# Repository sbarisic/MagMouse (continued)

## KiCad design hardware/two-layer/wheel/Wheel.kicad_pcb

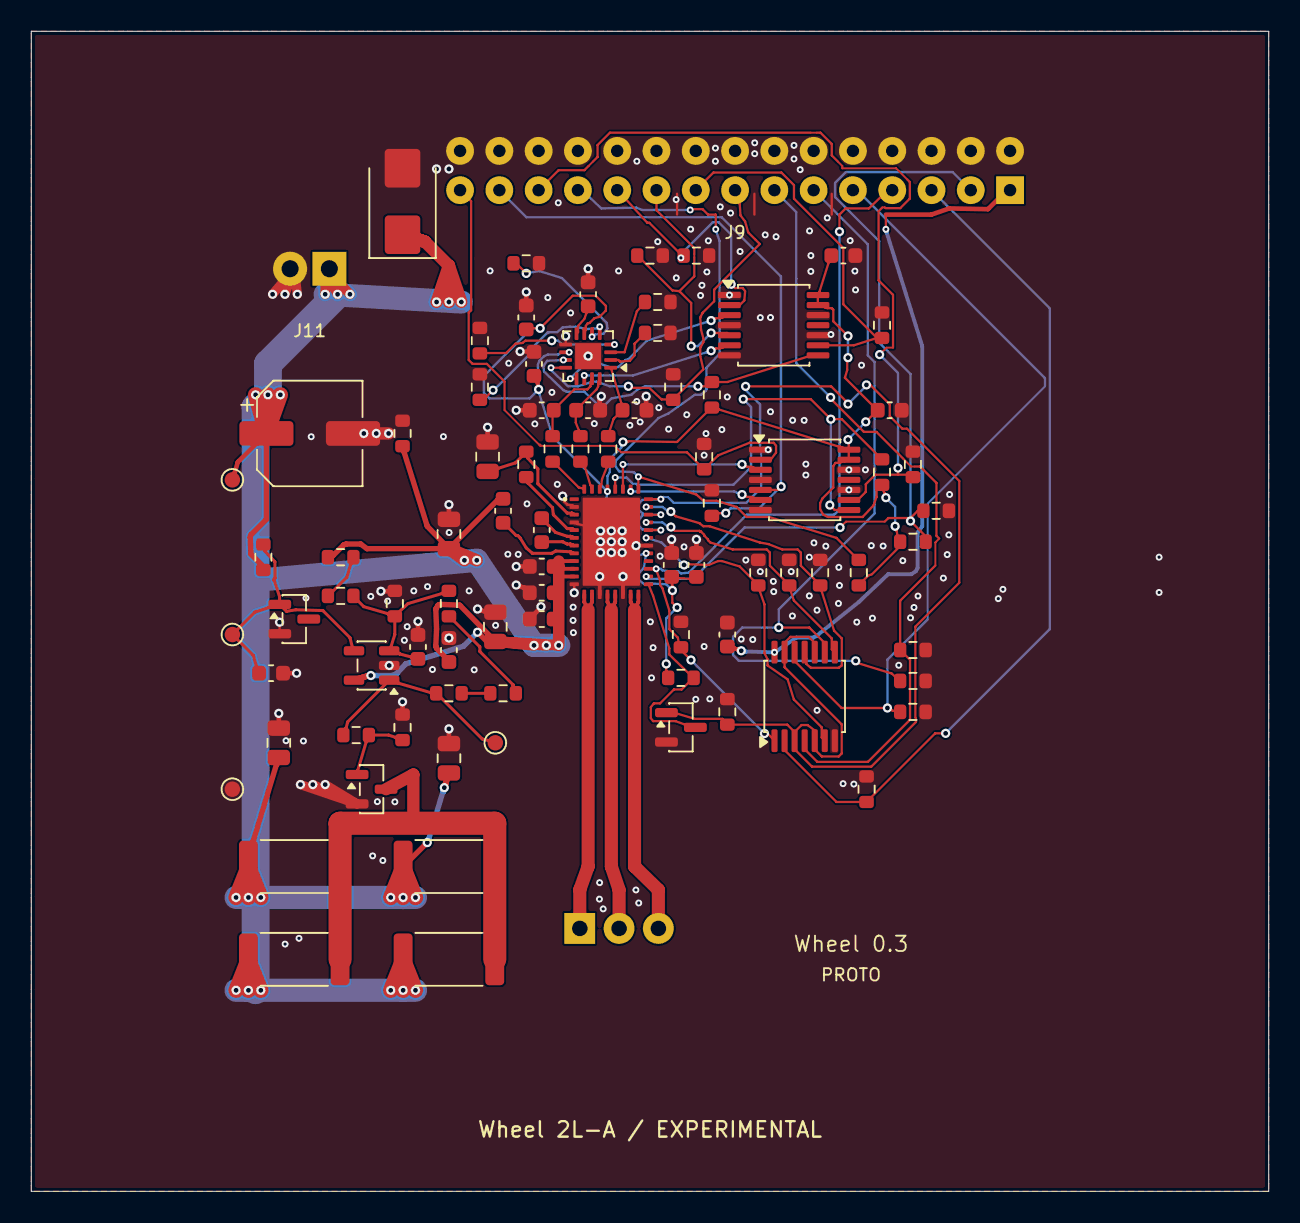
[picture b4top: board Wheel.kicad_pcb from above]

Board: 2 copper layers, 80.0 x 75.0 mm, 87 parts (0 on the bottom side), 57 nets.

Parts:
C41, C42, C43, C49, C51, C52, C54, C65, C66: 100nF; C_0603_1608Metric
C44, C45, C68, C69: 10uF/25V; C_0805_2012Metric
C46, C48, C56, C57, C58: 1uF/50V; C_0603_1608Metric
C47: 47nF/50V; C_0603_1608Metric
C50: 22uF/25V; C_0805_2012Metric
C59, C60, C61, C67: 22pF/50V; C_0603_1608Metric
C90: 100uF/16V; CP_Elec_6.3x5.9
D6: SMBJ6.0A; D_SMB
J5: GB1806 phase wires; MotorWire_3x1mm_P2.54mm
J9: Soldered wires Signal_2x15; Wire_Signal_2x15_P2.54mm
J11: Soldered wires Power_1x02; Wire_Power_1x02_P2.54mm
Q4: 2N7002; SOT-23
Q5: AO3400A; SOT-23
R81: 22R; R_0603_1608Metric
R82, R84, R86, R98, R111, R137, R138, R139, R140: 10k; R_0603_1608Metric
R83, R89, R90, R91, R92, R94, R95, R96, R97, R100, R112, R114, R120: 100k; R_0603_1608Metric
R87, R88, R146: 4.7k; R_0603_1608Metric
R102, R103, R104: 330R; R_0603_1608Metric
R105, R106, R107, R108, R109: 0R; R_0603_1608Metric
R113: 34.8k; R_0603_1608Metric
R115, R116, R117: 1M; R_0603_1608Metric
R119: 100R; R_0603_1608Metric
R121, R122, R123, R124: 47R/2W; R_2512_6332Metric
R144, R145: 33k; R_0603_1608Metric
TP34: ACT_5V; TestPoint_Pad_D1.0mm
TP35: BRAKE_REF; TestPoint_Pad_D1.0mm
TP36: BRAKE_OUT; TestPoint_Pad_D1.0mm
TP37: GND; TestPoint_Pad_D1.0mm
U21: DRV8316RRGFR; Texas_RGF0040E
U22: SN74LVC08APWR; TSSOP-14_4.4x5mm_P0.65mm
U23: ADS7038IRTER; WQFN-16-1EP_3x3mm_P0.5mm_EP1.68x1.68mm
U24, U26: SN74LVC125APWR; TSSOP-14_4.4x5mm_P0.65mm
U30: TLV1811DBVR; SOT-23-5
U31: LM4040AIM3-2.5/NOPB; SOT-23

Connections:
+3V3: C51.1, J9.1, U22.14
ACT_5V: C41.1, C42.1, C43.1, C44.1, C45.1, C46.2, C65.1, C68.1, C69.1, C90.1, D6.1, J11.1, R111.1, R112.1, R121.1, R122.1, R123.1, R124.1, R146.1, TP34.1, U21.9, U21.10, U21.11, U30.5
ACT_DRIVE_EN: J9.7, R84.1, U21.23, U22.1
ADC2_CS_LOCAL: R98.2, U23.11, U26.8
ADC2_DECAP: C58.1, U23.8
ADC2_MISO_LOCAL: J9.15, R100.1, U23.12
ADC2_MOSI_LOCAL: U23.14, U26.6
ADC2_SCLK_LOCAL: U23.13, U26.3
ADC2_SPARE3: R105.1, U23.2
ADC2_SPARE4: R106.1, U23.3
ADC2_SPARE5: R107.1, U23.4
ADC2_SPARE6: R108.1, U23.5
ADC2_SPARE7: R109.1, U23.6
BRAKE_DIV_TOP: R112.2, R113.1
BRAKE_DRAIN: Q5.3, R121.2, R122.2, R123.2, R124.2
BRAKE_FB_1: R115.2, R116.1
BRAKE_FB_2: R116.2, R117.1
BRAKE_GATE: Q5.1, R119.2, R120.1
BRAKE_OUT: R115.1, R119.1, TP36.1, U30.1
BRAKE_REF: C66.1, R111.2, TP35.1, U30.4, U31.1
BRAKE_SENSE: C67.1, R113.2, R114.1, R117.2, U30.3
CS_ADC2: J9.17, R145.1, U26.9
CS_DRV8316: J9.25, R144.1, U24.9
DRV_AVDD: C48.1, C49.1, C52.1, C54.1, C56.1, C57.1, R82.1, R86.1, R87.1, R88.1, R98.1, U21.25, U21.37, U23.7, U23.10, U24.13, U24.14, U26.13, U26.14
DRV_CS_LOCAL: R86.2, U21.36, U24.8
DRV_FAULT_LOCAL_N: J9.3, R88.2, R89.1, U21.22
DRV_INHA: R90.1, U21.27, U22.6
DRV_INHB: R91.1, U21.29, U22.8
DRV_INHC: R92.1, U21.31, U22.11
DRV_MISO_LOCAL: J9.23, R87.2, U21.33
DRV_MOSI_LOCAL: U21.34, U24.6
DRV_SCLK_LOCAL: U21.35, U24.3
GND: C41.2, C42.2, C43.2, C44.2, C45.2, C48.2, C49.2, C50.2, C51.2, C52.2, C54.2, C56.2, C57.2, C58.2, C59.2, C60.2, C61.2, C65.2, C66.2, C67.2, C68.2, C69.2, C90.2, D6.2, J9.2, J9.4, J9.6, J9.8, J9.10, J9.12, J9.14, J9.16, J9.18, J9.20, J9.22, J9.24, J9.26, J9.28, J9.30, J11.2, Q4.2, Q5.2, R83.2, R84.2, R89.2, R90.2, R91.2, R92.2, R94.2, R95.2, R96.2, R97.2, R100.2, R105.2, R106.2, R107.2, R108.2, R109.2, R114.2, R120.2, R137.2, R138.2, R139.2, R140.2, R144.2, R145.2, R146.2, TP37.1, U21.2, U21.4, U21.12, U21.15, U21.18, U21.26, U21.41, U22.7, U23.9, U23.17, U24.1, U24.4, U24.7, U24.10, U24.12, U26.1, U26.4, U26.7, U26.10, U26.12, U30.2, U31.2
MOTOR_SPI_MOSI: J9.19, R97.1, U26.5
MOTOR_SPI_SCLK: J9.21, R96.1, U26.2
SPI_MOSI: J9.27, R95.1, U24.5
SPI_SCLK: J9.29, R94.1, U24.2
WHEEL_BUCK_OUT: C50.1, R81.2, U21.3
WHEEL_BUCK_SW: R81.1, U21.5
WHEEL_CP: C46.1, U21.8
WHEEL_CPH: C47.1, U21.7
WHEEL_CPL: C47.2, U21.6
WHEEL_DRVOFF: Q4.3, R82.2, U21.21
WHEEL_I_A: C59.1, R102.2, U23.15
WHEEL_I_B: C60.1, R103.2, U23.16
WHEEL_I_C: C61.1, R104.2, U23.1
WHEEL_PHASE_A: J5.1, U21.13, U21.14
WHEEL_PHASE_B: J5.2, U21.16, U21.17
WHEEL_PHASE_C: J5.3, U21.19, U21.20
WHEEL_PWM_A: J9.13, R138.1, U22.4
WHEEL_PWM_B: J9.11, R139.1, U22.9
WHEEL_PWM_C: J9.9, R140.1, U22.12
WHEEL_RUN_EN: Q4.1, R83.1, U21.28, U21.30, U21.32, U22.3, U22.5, U22.10, U22.13
WHEEL_RUN_REQ: J9.5, R137.1, U22.2
WHEEL_SOA: R102.1, U21.40
WHEEL_SOB: R103.1, U21.39
WHEEL_SOC: R104.1, U21.38

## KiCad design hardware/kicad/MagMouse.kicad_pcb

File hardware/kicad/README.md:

# KiCad electronics

This directory is the **retained monolithic reference**. Current work uses the
independent [Main project](../modular/main/Main.kicad_pro) and
[Wheel project](../modular/wheel/Wheel.kicad_pro), both now routed with zero
unrouted/DRC/parity issues. See the [modular package](../modular/README.md).
The revision and instructions below describe the older reference project.

Revision 0.8, 2026-09-09, KiCad 10.0.6. USB-C power, MCU allocation and wheel/brake, IMU, RGB and PMW3360 circuits are connected.
A [60 x 95 mm motherboard placement](../pcb/README.md) is available as of
2026-09-09, with all 317 footprints on-board. U27/C62 and J7 are in a separate,
fully routed [14 x 18 mm encoder project](../encoder/README.md). Both are editable
development drafts; **the motherboard is partially routed and neither board is
order-ready**. Firmware, measurements and mechanical fit remain open.

## Open the retained reference

1. Open [MagMouse.kicad_pro](MagMouse.kicad_pro) in KiCad Manager.
2. Open [MagMouse.kicad_sch](MagMouse.kicad_sch).
3. Enter a sheet and press **E** on a component to inspect its MPN, footprint,
   LCSC number and sourcing status.
4. Open [MagMouse.kicad_pcb](MagMouse.kicad_pcb) in PCB Editor for the initial
   layout. Enable Dwgs.User for reservations and F.Fab/B.Fab for references.

Use the standard KiCad 10 libraries. The local symbol and footprint libraries
are registered by [sym-lib-table](sym-lib-table) and [fp-lib-table](fp-lib-table).
No JLCPCB plugin is needed. Edit the schematic files directly.

| Sheet | Implemented content |
| --- | --- |
| Overview | Eighteen-page hierarchy and remaining work |
| 01 Power / USB | USB-C data/CC protection, TUSB320 sink detection, TPS62162 fixed 3.3 V regulator |
| 02 MCU | ESP32-S3 module, USB, reset/boot, recovery pads and power-control GPIOs |
| 03 Buttons | Three DRV8231A bridges, VREF/current feedback, input pulldowns and coil connectors |
| 04 Sensing | Three switchable Hall sensors, ADS7038; all eight ADC channels assigned |
| 05 Protected power | Separate input/actuator eFuses, UVLO/OVLO, ramps, fault/reset and enable clamp |
| 06 Actuator interlock | Hardware heartbeat timeout, source/reset/sensor-qualified arm and six input gates |
| 07 Power monitor | CC-selected current-limit resistors, buffered input-current sensing, VBUS presence and ACT voltage |
| 08 Actuator rail | Input/actuator transient clamps, ACT storage/discharge and test pads |
| 09 Interface reservations | MCU interfaces, test pads and boot/control bias |
| 10 Wheel driver | DRV8316R, 3-PWM hardware shutdown, charge pump, unused-buck termination and motor wire pads |
| 11 Wheel SPI | Driver/ADC2/encoder power-domain buffers and fault return |
| 12 Wheel feedback | Second ADS7038, phase-current filters, switched encoder supply and J6 cable header |
| 13 Regeneration brake | ACT-powered comparator/reference, MOSFET and four power resistors |
| 14 IMU | ICM-42688-P, shared SPI2, INT1 and supply bypass |
| 15 RGB status | Single-data-pin LED, enabled regulator and logic buffer |
| 16 Optical power | Sensor-enabled ramp switch, 1.9V LDO, illumination feed and bypass |
| 17 Optical sensor | PMW3360, isolated SPI/CS and strong reset buffer |

VBUS_USB feeds PWR_5V through U12; U13 supplies ACT_5V. These rails replace the
disconnected pending nets. The TPS62162 and 3.3 uH inductor replace the original
TLV62569/divider circuit. See [power behavior and firmware requirements](../../docs/power.md)
and [power sourcing/package review](POWER_REVIEW.md).

Each button bridge retains the provisional 0.333 A trip setting:
1.65 V / (0.0015 × 3300 ohms). Actual force, current accuracy, winding heating
and pulse duration require the mechanical experiment. Coils, magnets, paddles
and wiring are external assemblies, not SMT parts.

## Review exports

From the repository root, run these commands with Python 3 and KiCad 10:

    python hardware/kicad/export_review.py
    python hardware/kicad/export_review.py --schematic hardware/encoder/Encoder.kicad_sch
    python hardware/kicad/verify_encoder.py
    python hardware/kicad/test_encoder_checks.py
    python hardware/kicad/verify_power.py
    python hardware/kicad/verify_resources.py
    python hardware/kicad/verify_wheel.py
    python hardware/kicad/test_wheel_checks.py
    python hardware/kicad/verify_peripherals.py
    python hardware/kicad/test_peripheral_checks.py
    python hardware/kicad/verify_optical.py
    python hardware/kicad/test_optical_checks.py

The exporter accepts --kicad-cli PATH. The checker accepts --footprints PATH
for a nonstandard KiCad footprint installation. Generated files go to
build/kicad-review: eighteen SVG sheets, XML netlist, ERC JSON, DRAFT-bom.csv,
review-status.json, power-checks.json, resource-checks.json, wheel-checks.json, peripheral-checks.json and optical-checks.json. Sources are not overwritten.

The motherboard has **273 BOM components**, all with catalog IDs, MPNs and
footprints; 43 copper test pads, J5 motor wire pads and four power flags are
excluded from its BOM. The separate encoder has one schematic sheet and three
BOM components/footprints: U27, C62 and J7. Across both projects there are 19
schematic pages, 276 BOM components and 320 footprints. Encoder review outputs
and its separate draft BOM go to `build/encoder-review`; its two incoming power
flags are excluded from assembly. Export both netlists before running the wheel
checker. The encoder checker also verifies the actual harness contract.
**Both projects: ERC zero errors and zero warnings, without new waivers.**
The additional checker verifies 195 critical power pin connections, 317 motherboard footprint
assignments, complete source-to-export coverage and 4,096 Boolean interlock
cases. The resource checker verifies all 39 module GPIOs: 38 assigned and GPIO46
reserved low for boot-safe expansion. See [the full allocation](../../docs/interfaces.md).
The wheel checker adds 266 pin checks, 32 shutdown cases, 58 custom land checks
and 128 brake corners; five wheel tests include four fault injections.
Optical adds 81 pin checks, ten identities, 16 land coordinates and eight fault injections.
See [optical implementation](OPTICAL_DESIGN.md) for pending sample and firmware evidence.
See [wheel design and evidence](WHEEL_REVIEW.md) and [IMU/RGB review](PERIPHERAL_REVIEW.md). Analog timing, firmware
deadlines, thermal behavior and USB compliance are not simulated.

Catalog identity does not reserve stock. U11's current JLCPCB listing requires
Standard PCBA; refresh service eligibility and pricing before placing an order.
These schematic tools do not produce manufacturing files. Use
`python hardware/kicad/export_pcb_review.py` for the separate PCB placement/DRC
review; see [board setup and remaining layout work](../pcb/README.md).
The first [buck routing pass](../pcb/BUCK_LAYOUT.md) also provides native copper
connectivity checks and fault-injection tests, run with KiCad's bundled Python.

## Work before full-board freeze

A bench prototype and preliminary placement can proceed before all measurements
are complete. Full-mouse routing needs settled circuitry, pin allocation and
mechanical dimensions. The following tests are acceptance gates, including tests
that require a prototype PCB; finished firmware is not required to start layout.

- Implement and measure USB startup, configuration, suspend/resume and source
  changes. Verify the 100 mA startup and 2.5 mA suspend requirements.
- Prototype one button; measure force/current, winding properties, current-sense
  accuracy, heating, passive return and magnetic interference.
- Test timeout/reset/short-circuit behavior, cable drop, inrush, reverse current,
  regenerative clamp behavior and component temperatures.
- Qualify the [PMW3360 circuit](OPTICAL_DESIGN.md), samples, SROM and optical stack.
  Review and measure the [IMU/RGB circuits](PERIPHERAL_REVIEW.md). Validate wheel current/angle
  acquisition and the provisional autonomous regeneration brake on hardware.
- Validate the [allocated SPI/PWM timing budgets](../../docs/interfaces.md), review symbols,
  land patterns and stencil requirements, then perform board layout and DRC.

See [SOURCING.md](SOURCING.md) for retained component evidence and
[the roadmap](../../docs/roadmap.md) for the broader project.

The [input-power routing pass](../pcb/INPUT_POWER_LAYOUT.md) adds C88,
USB-to-eFuse-to-buck copper, protection and source-selection routes, and
a board-wide In1 ground reference. USB geometry is recorded in the
[selected stackup](../pcb/STACKUP.md); the [USB/ILM pass](../pcb/USB_LAYOUT.md)
now routes the pair over continuously checked In1 ground. Full-board routing remains open.

The [Type-C routing pass](../pcb/TYPEC_LAYOUT.md) completes the detector inputs,
returns and source-selection supplies. The [U13 local routing pass](../pcb/ACTUATOR_POWER_LAYOUT.md)
adds C89 and connects its feed, bypass and protection network. Native connectivity
has 204 unrouted connections after the [USB/ILM pass](../pcb/USB_LAYOUT.md).
Actuator feeds, driver/brake outputs, current sensing, interlocks and gate supplies
are connected and checked, as are USB data and buffered input-current telemetry.
SPI, optical and remaining board routing are open.
Six component-land vias at U1/C32/U21 require filled/capped fabrication and stencil review.

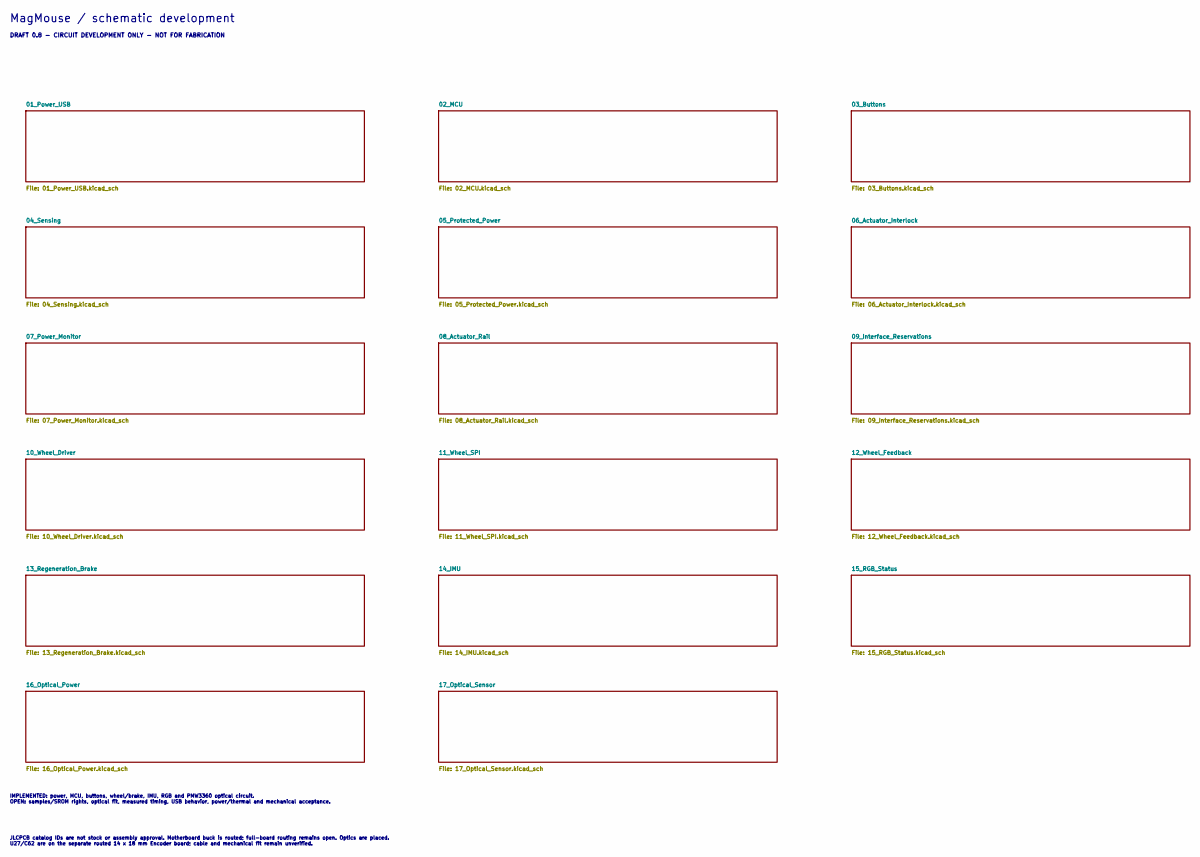
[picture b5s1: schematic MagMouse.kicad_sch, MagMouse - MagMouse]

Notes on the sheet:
MagMouse / schematic development
DRAFT 0.8 - CIRCUIT DEVELOPMENT ONLY - NOT FOR FABRICATION
IMPLEMENTED: power, MCU, buttons, wheel/brake, IMU, RGB and PMW3360 optical circuit. OPEN: samples/SROM rights, optical fit, measured timing, USB behavior, power/thermal and mechanical acceptance.
JLCPCB catalog IDs are not stock or assembly approval. Motherboard buck is routed; full-board routing remains open. Optics are placed. U27/C62 are on the separate routed 14 x 18 mm Encoder board; cable and mechanical fit remain unverified.

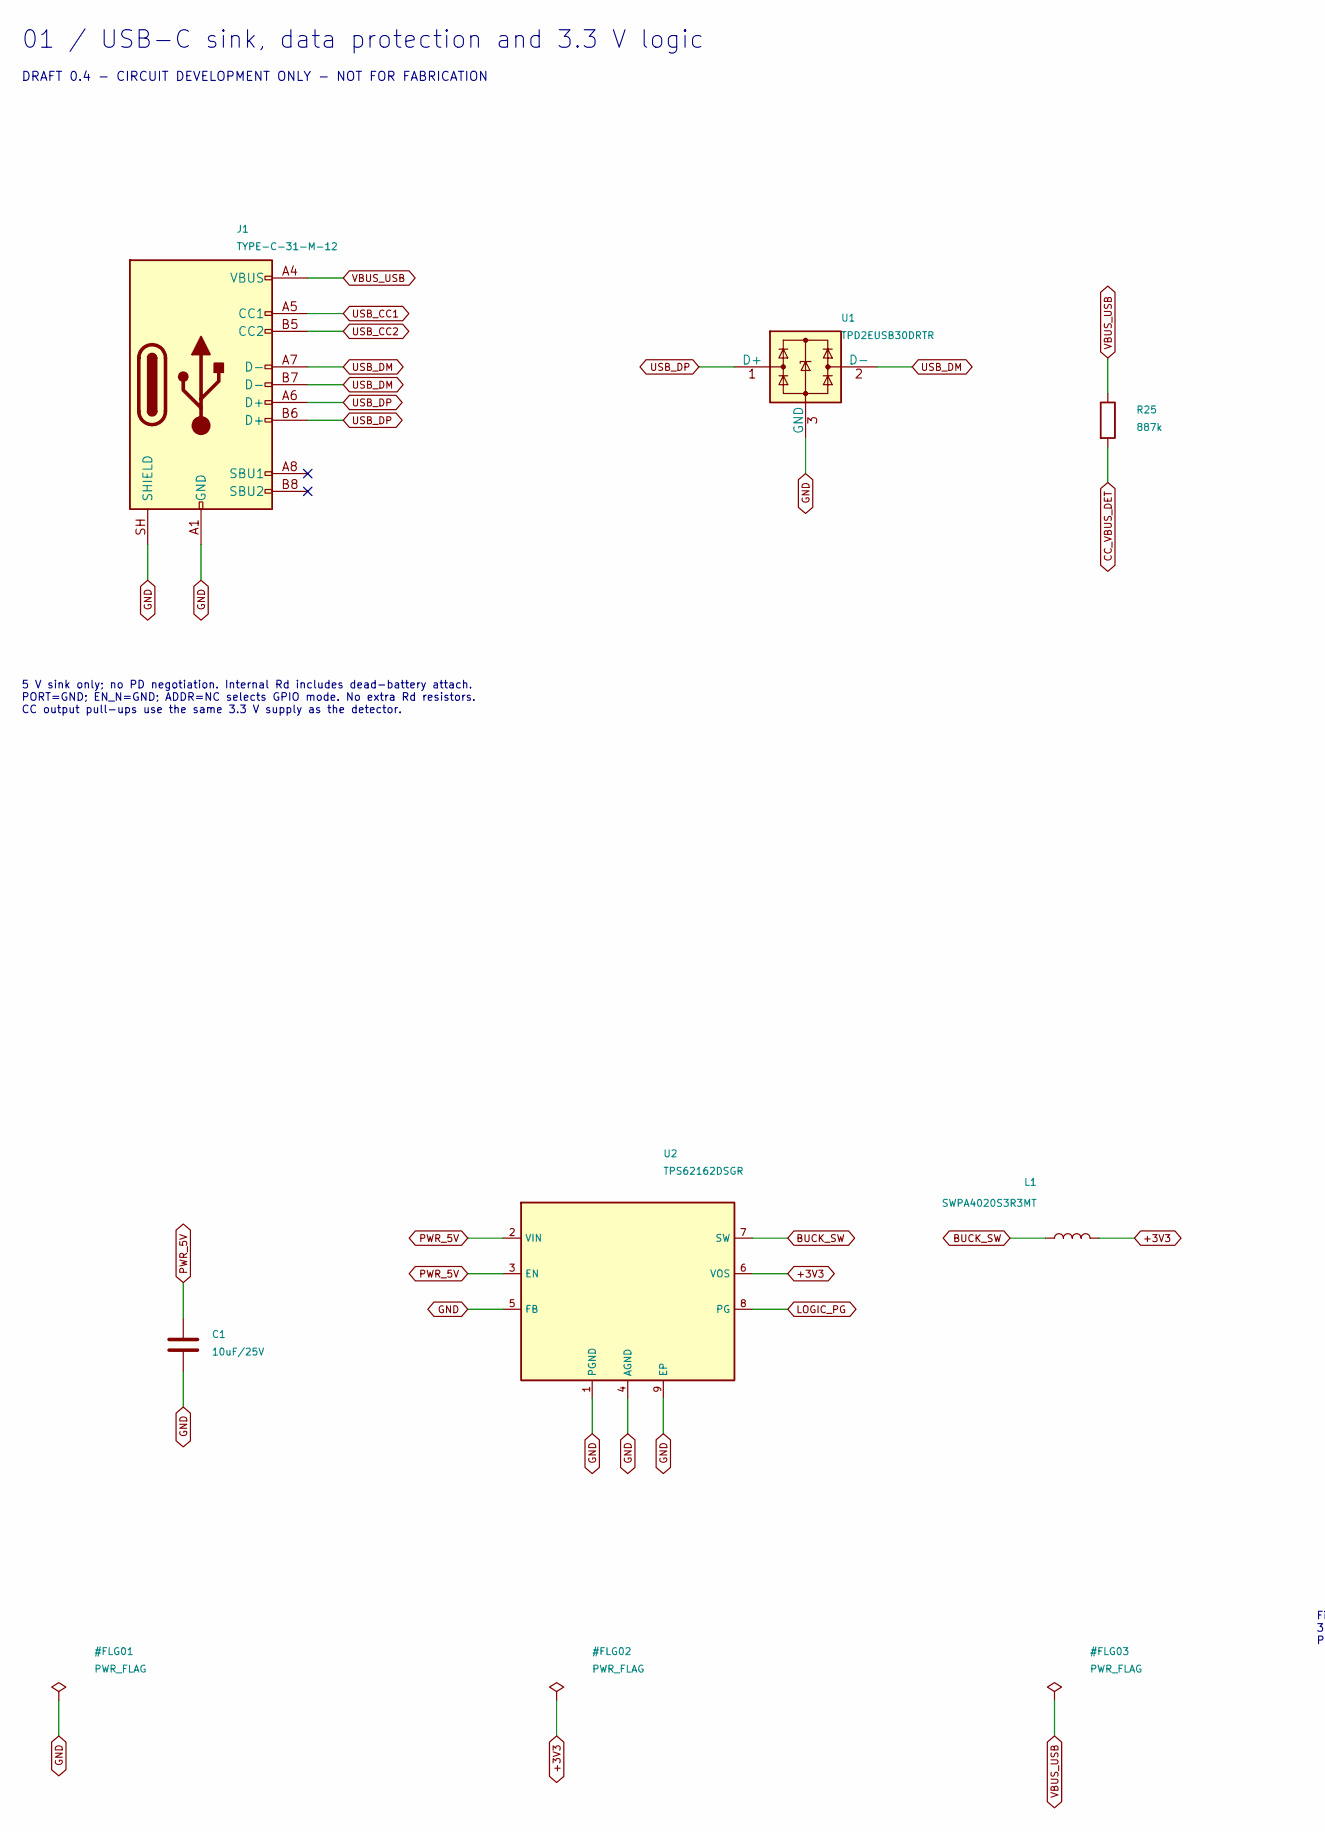
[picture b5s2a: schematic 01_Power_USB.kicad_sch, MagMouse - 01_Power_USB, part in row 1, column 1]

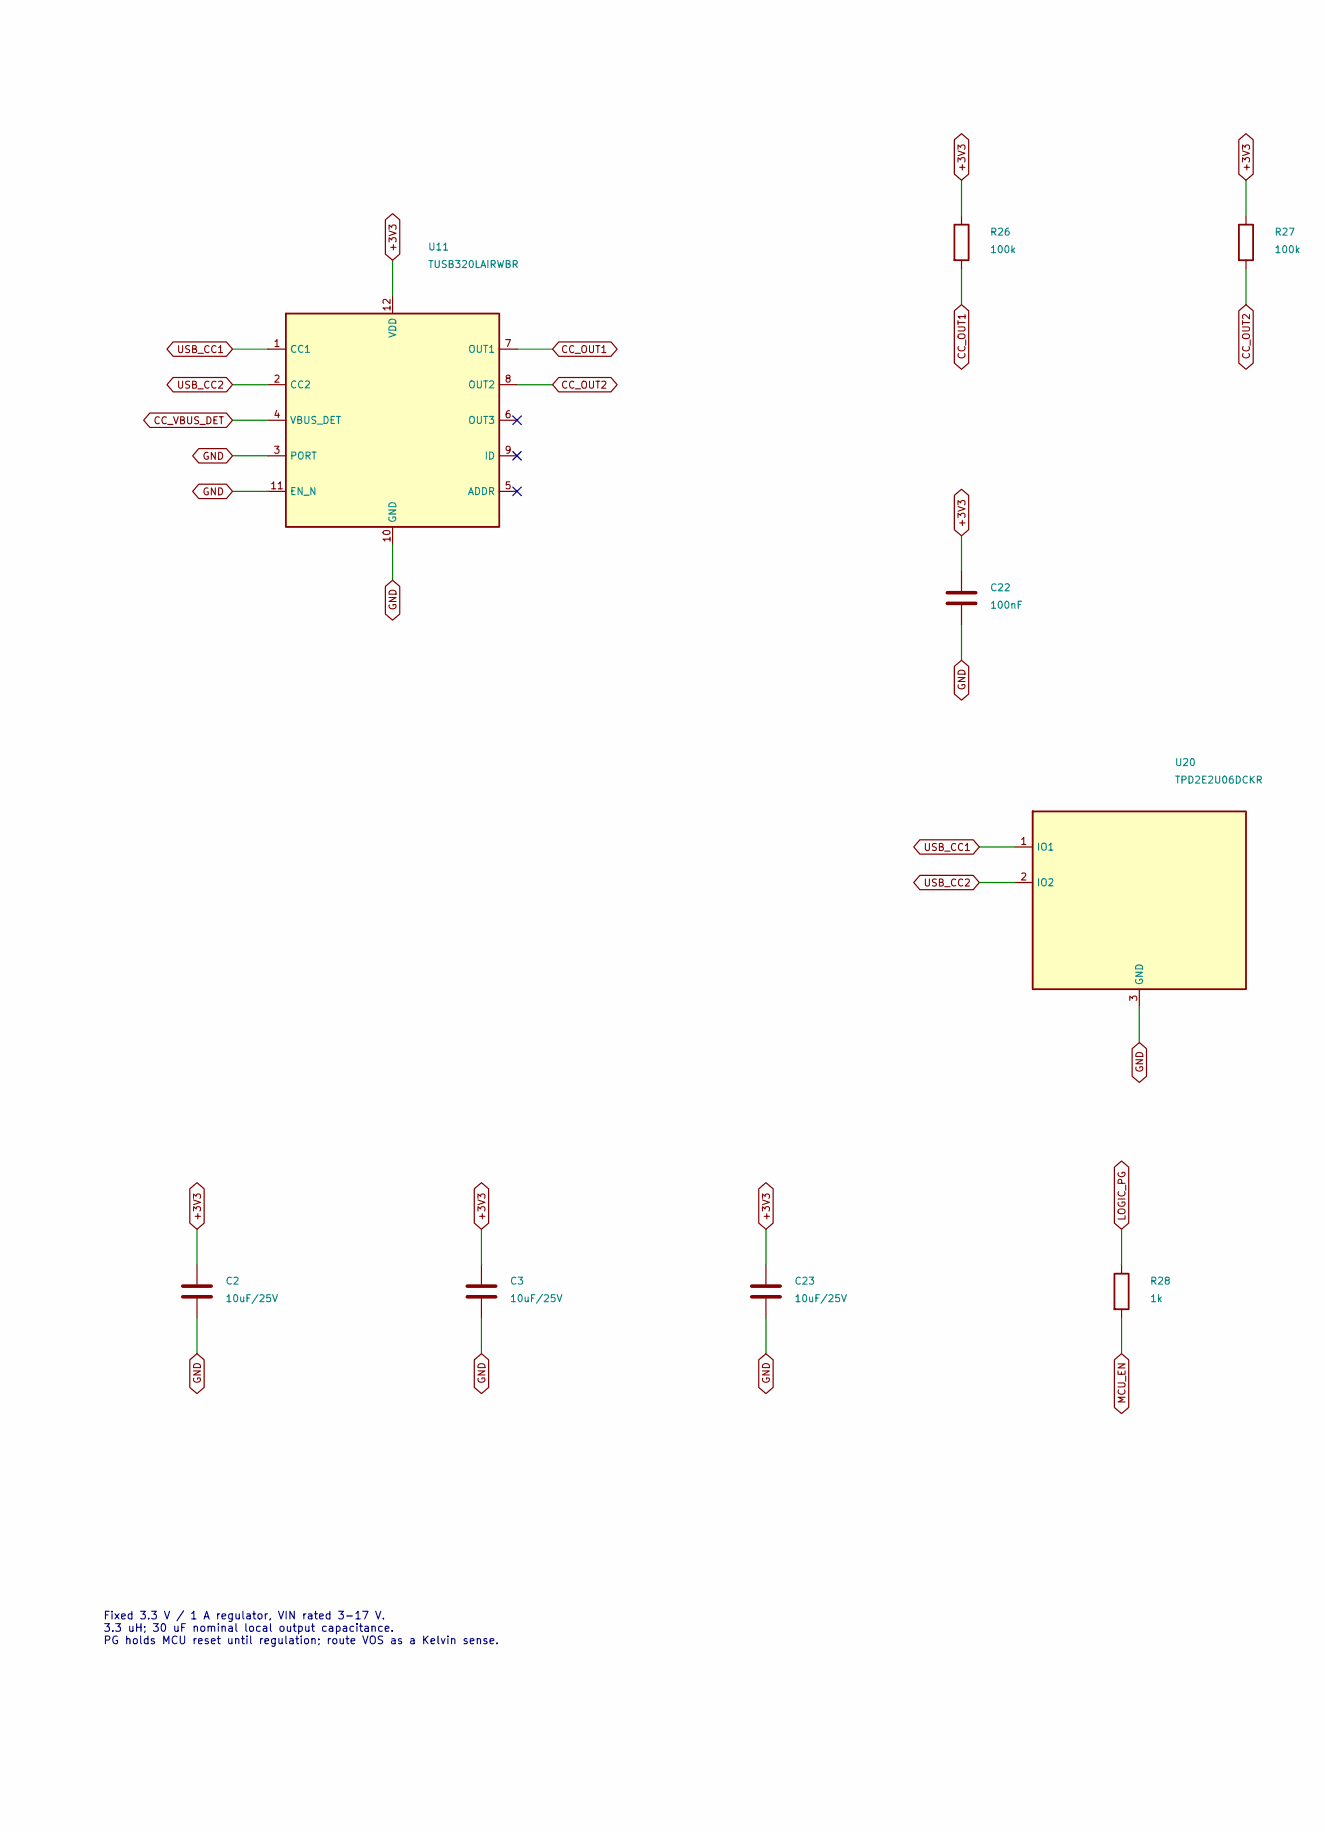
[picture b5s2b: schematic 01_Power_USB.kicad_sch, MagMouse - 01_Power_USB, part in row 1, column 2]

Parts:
C1, C2, C3, C23: 10uF/25V; C_0805_2012Metric; MPN CL21A106KAYNNNE; LCSC C15850
C22: 100nF; C_0603_1608Metric; MPN CC0603KRX7R9BB104; LCSC C14663
J1: TYPE-C-31-M-12; USB_C_Receptacle_HRO_TYPE-C-31-M-12; MPN TYPE-C-31-M-12; LCSC C165948
L1: SWPA4020S3R3MT; L_Sunlord_SWPA4020S; MPN SWPA4020S3R3MT; LCSC C83424
R25: 887k; R_0603_1608Metric; MPN 0603WAF8873T5E; LCSC C23259
R26, R27: 100k; R_0603_1608Metric; MPN 0603WAF1003T5E; LCSC C25803
R28: 1k; R_0603_1608Metric; MPN 0603WAF1001T5E; LCSC C21190
U1: TPD2EUSB30DRTR; Texas_DRT-3; MPN TPD2EUSB30DRTR; LCSC C97502
U2: TPS62162DSGR; Texas_DSG0008A_WSON-8-1EP_2x2mm_P0.5mm_EP0.9x1.6mm; MPN TPS62162DSGR; LCSC C40256
U11: TUSB320LAIRWBR; Texas_X2QFN-12_1.6x1.6mm_P0.4mm; MPN TUSB320LAIRWBR; LCSC C132554
U20: TPD2E2U06DCKR; SOT-323_SC-70; MPN TPD2E2U06DCKR; LCSC C1855726

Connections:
+3V3: C2.1, C3.1, C22.1, C23.1, L1.2, R26.1, R27.1, U2.6 (VOS), U11.12 (VDD); also elsewhere on the board
BUCK_SW: L1.1, U2.7 (SW)
CC_OUT1: R26.2, U11.7 (OUT1); also elsewhere on the board
CC_OUT2: R27.2, U11.8 (OUT2); also elsewhere on the board
CC_VBUS_DET: R25.2, U11.4 (VBUS_DET)
GND: C1.2, C2.2, C3.2, C22.2, C23.2, J1.A1 (GND), J1.A12 (GND), J1.B1 (GND), J1.B12 (GND), J1.SH (SHIELD), U1.3 (GND), U2.1 (PGND), U2.4 (AGND), U2.5 (FB), U2.9 (EP), U11.3 (PORT), U11.10 (GND), U11.11 (EN_N), U20.3 (GND); also elsewhere on the board
LOGIC_PG: R28.1, U2.8 (PG)
MCU_EN: R28.2; also elsewhere on the board
PWR_5V: C1.1, U2.2 (VIN), U2.3 (EN); also elsewhere on the board
USB_CC1: J1.A5 (CC1), U11.1 (CC1), U20.1 (IO1)
USB_CC2: J1.B5 (CC2), U11.2 (CC2), U20.2 (IO2)
USB_DM: J1.A7 (D-), J1.B7 (D-), U1.2 (D-); also elsewhere on the board
USB_DP: J1.A6 (D+), J1.B6 (D+), U1.1 (D+); also elsewhere on the board
VBUS_USB: J1.A4 (VBUS), J1.A9 (VBUS), J1.B4 (VBUS), J1.B9 (VBUS), R25.1; also elsewhere on the board

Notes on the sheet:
01 / USB-C sink, data protection and 3.3 V logic
DRAFT 0.4 - CIRCUIT DEVELOPMENT ONLY - NOT FOR FABRICATION
Fixed 3.3 V / 1 A regulator, VIN rated 3-17 V. 3.3 uH; 30 uF nominal local output capacitance. PG holds MCU reset until regulation; route VOS as a Kelvin sense.
5 V sink only; no PD negotiation. Internal Rd includes dead-battery attach. PORT=GND; EN_N=GND; ADDR=NC selects GPIO mode. No extra Rd resistors. CC output pull-ups use the same 3.3 V supply as the detector.

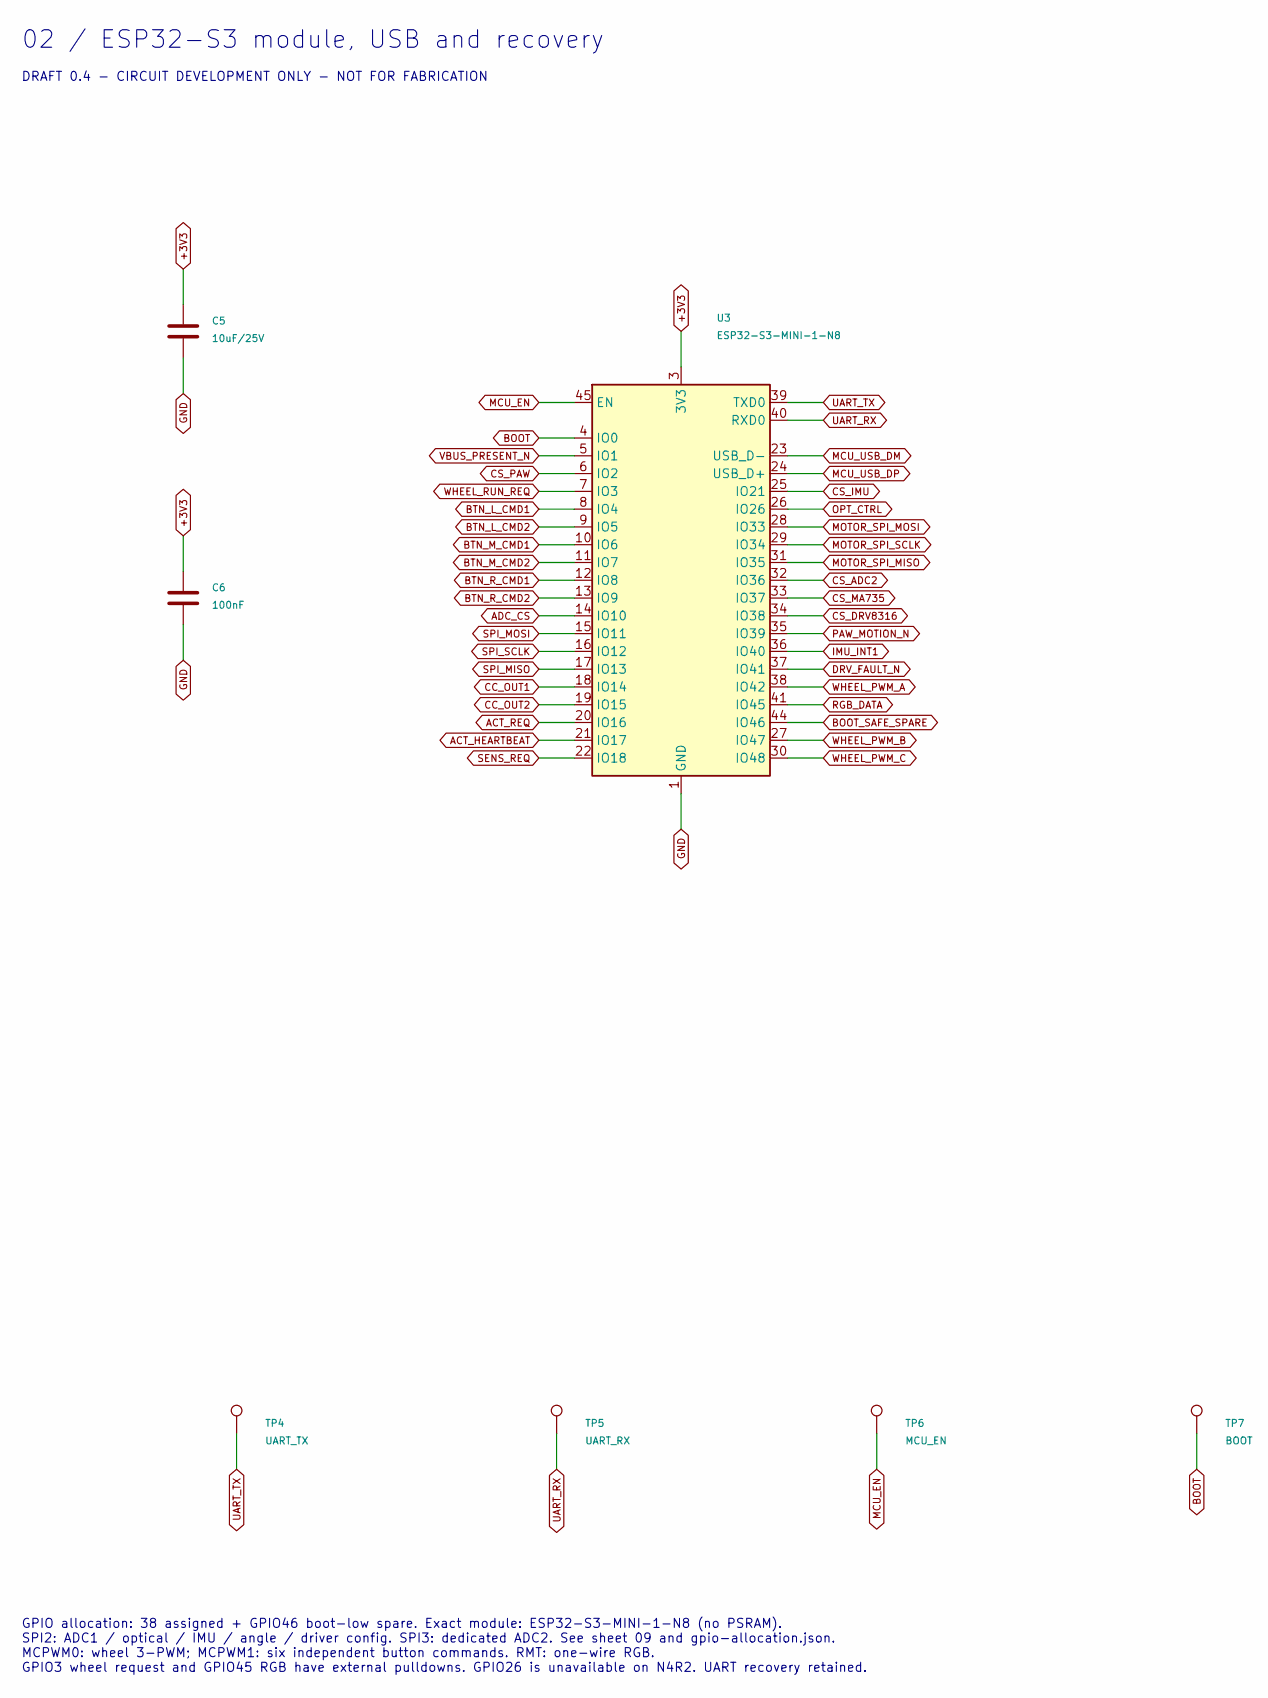
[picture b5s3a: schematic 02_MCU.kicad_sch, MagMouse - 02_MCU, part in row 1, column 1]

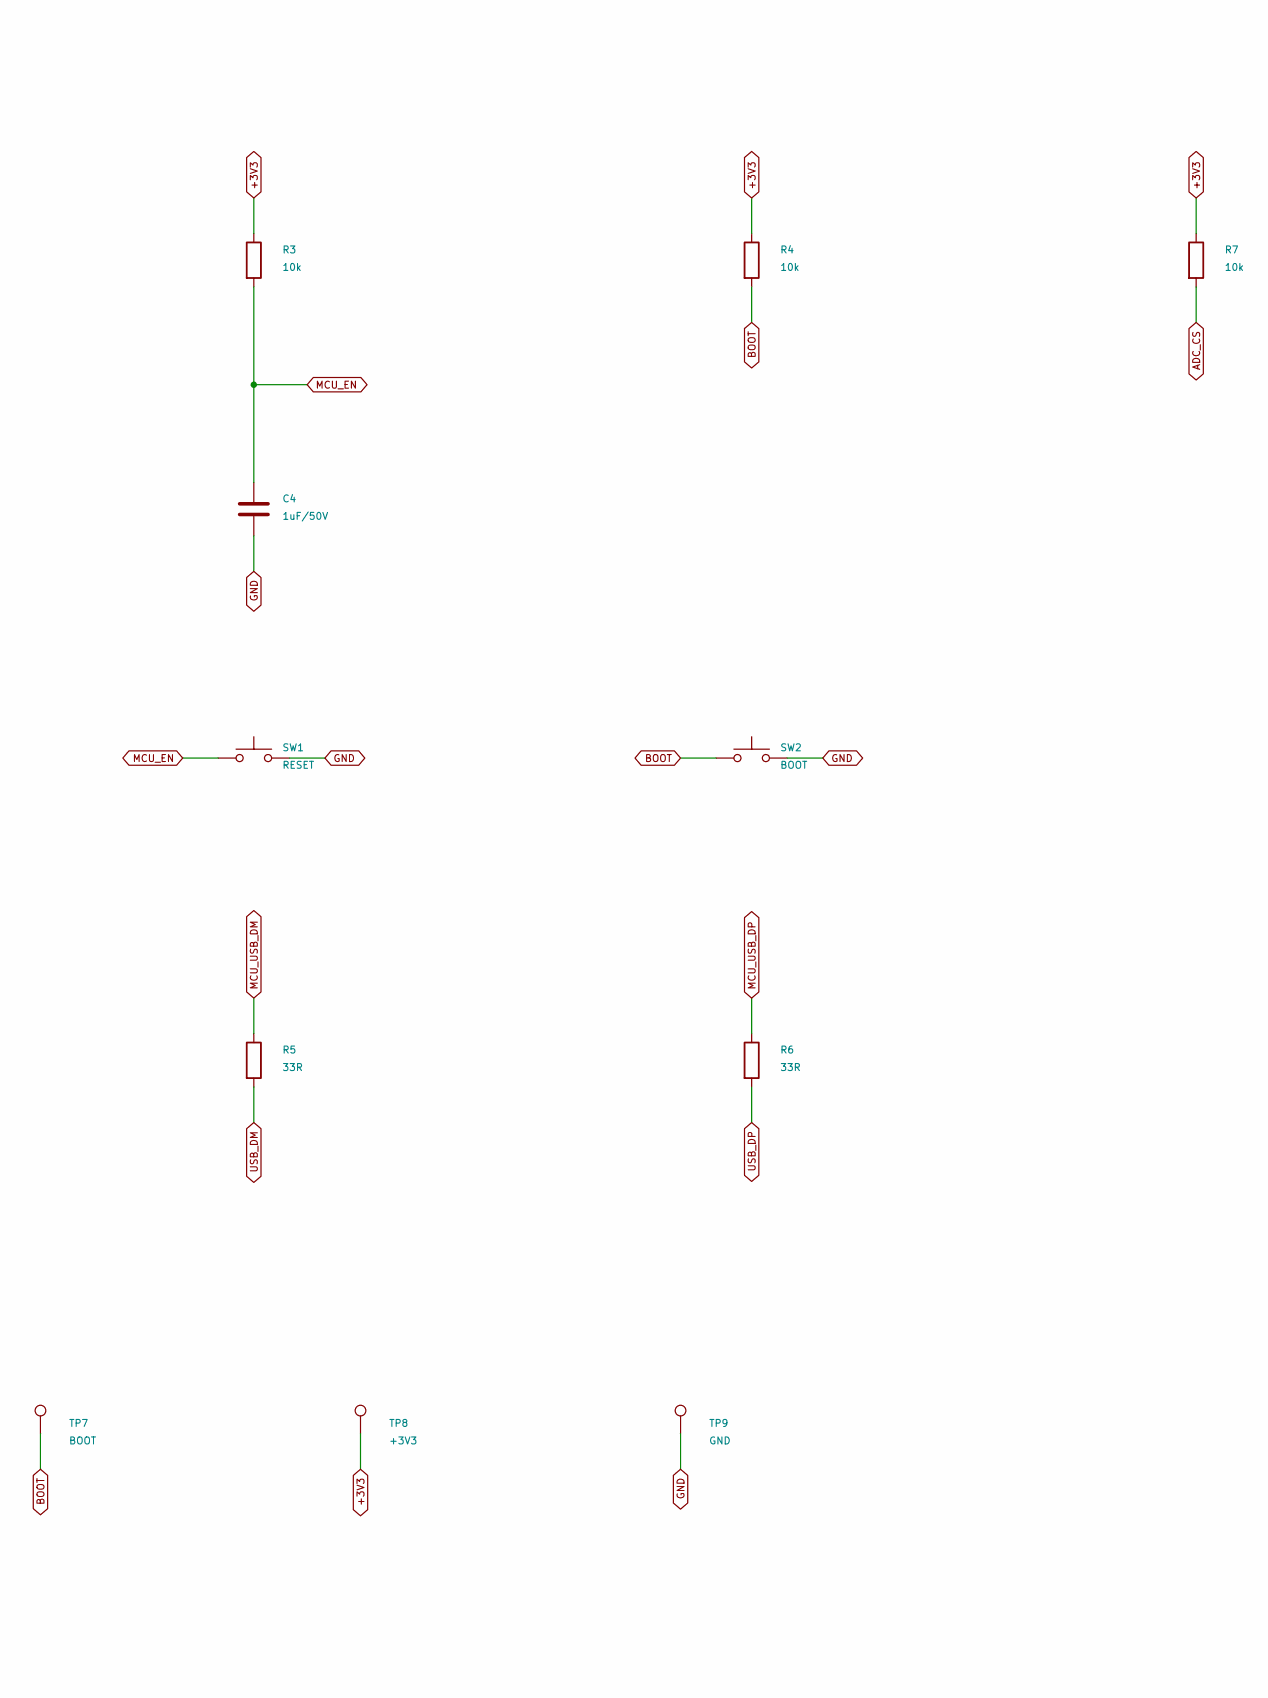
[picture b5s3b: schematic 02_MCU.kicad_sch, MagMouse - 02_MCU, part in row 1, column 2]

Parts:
C4: 1uF/50V; C_0603_1608Metric; MPN CL10A105KB8NNNC; LCSC C15849
C5: 10uF/25V; C_0805_2012Metric; MPN CL21A106KAYNNNE; LCSC C15850
C6: 100nF; C_0603_1608Metric; MPN CC0603KRX7R9BB104; LCSC C14663
R3, R4, R7: 10k; R_0603_1608Metric; MPN 0603WAF1002T5E; LCSC C25804
R5, R6: 33R; R_0603_1608Metric; MPN 0603WAF330JT5E; LCSC C23140
SW1: RESET; SW_SPST_TS-1088-xR020; MPN TS-1088-AR02016; LCSC C720477
SW2: BOOT; SW_SPST_TS-1088-xR020; MPN TS-1088-AR02016; LCSC C720477
TP4: UART_TX; TestPoint_Pad_D1.0mm
TP5: UART_RX; TestPoint_Pad_D1.0mm
TP6: MCU_EN; TestPoint_Pad_D1.0mm
TP7: BOOT; TestPoint_Pad_D1.0mm
TP8: +3V3; TestPoint_Pad_D1.0mm
TP9: GND; TestPoint_Pad_D1.0mm
U3: ESP32-S3-MINI-1-N8; ESP32-S2-MINI-1; MPN ESP32-S3-MINI-1-N8; LCSC C2913206

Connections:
+3V3: C5.1, C6.1, R3.1, R4.1, R7.1, TP8.1, U3.3 (3V3); also elsewhere on the board
ACT_HEARTBEAT: U3.21 (IO17); also elsewhere on the board
ACT_REQ: U3.20 (IO16); also elsewhere on the board
ADC_CS: R7.2, U3.14 (IO10); also elsewhere on the board
BOOT: R4.2, SW2.1, TP7.1, U3.4 (IO0)
BOOT_SAFE_SPARE: U3.44 (IO46); also elsewhere on the board
BTN_L_CMD1: U3.8 (IO4); also elsewhere on the board
BTN_L_CMD2: U3.9 (IO5); also elsewhere on the board
BTN_M_CMD1: U3.10 (IO6); also elsewhere on the board
BTN_M_CMD2: U3.11 (IO7); also elsewhere on the board
BTN_R_CMD1: U3.12 (IO8); also elsewhere on the board
BTN_R_CMD2: U3.13 (IO9); also elsewhere on the board
CC_OUT1: U3.18 (IO14); also elsewhere on the board
CC_OUT2: U3.19 (IO15); also elsewhere on the board
CS_ADC2: U3.32 (IO36); also elsewhere on the board
CS_DRV8316: U3.34 (IO38); also elsewhere on the board
CS_IMU: U3.25 (IO21); also elsewhere on the board
CS_MA735: U3.33 (IO37); also elsewhere on the board
CS_PAW: U3.6 (IO2); also elsewhere on the board
DRV_FAULT_N: U3.37 (IO41); also elsewhere on the board
GND: C4.2, C5.2, C6.2, SW1.2, SW2.2, TP9.1, U3.1 (GND), U3.2 (GND), U3.42 (GND), U3.43 (GND), U3.46 (GND), U3.47 (GND), U3.48 (GND), U3.49 (GND), U3.50 (GND), U3.51 (GND), U3.52 (GND), U3.53 (GND), U3.54 (GND), U3.55 (GND), U3.56 (GND), U3.57 (GND), U3.58 (GND), U3.59 (GND), U3.60 (GND), U3.61 (GND), U3.62 (GND), U3.63 (GND), U3.64 (GND), U3.65 (GND); also elsewhere on the board
IMU_INT1: U3.36 (IO40); also elsewhere on the board
MCU_EN: C4.1, R3.2, SW1.1, TP6.1, U3.45 (EN); also elsewhere on the board
MCU_USB_DM: R5.1, U3.23 (USB_D-)
MCU_USB_DP: R6.1, U3.24 (USB_D+)
MOTOR_SPI_MISO: U3.31 (IO35); also elsewhere on the board
MOTOR_SPI_MOSI: U3.28 (IO33); also elsewhere on the board
MOTOR_SPI_SCLK: U3.29 (IO34); also elsewhere on the board
OPT_CTRL: U3.26 (IO26); also elsewhere on the board
PAW_MOTION_N: U3.35 (IO39); also elsewhere on the board
RGB_DATA: U3.41 (IO45); also elsewhere on the board
SENS_REQ: U3.22 (IO18); also elsewhere on the board
SPI_MISO: U3.17 (IO13); also elsewhere on the board
SPI_MOSI: U3.15 (IO11); also elsewhere on the board
SPI_SCLK: U3.16 (IO12); also elsewhere on the board
UART_RX: TP5.1, U3.40 (RXD0)
UART_TX: TP4.1, U3.39 (TXD0)
USB_DM: R5.2; also elsewhere on the board
USB_DP: R6.2; also elsewhere on the board
VBUS_PRESENT_N: U3.5 (IO1); also elsewhere on the board
WHEEL_PWM_A: U3.38 (IO42); also elsewhere on the board
WHEEL_PWM_B: U3.27 (IO47); also elsewhere on the board
WHEEL_PWM_C: U3.30 (IO48); also elsewhere on the board
WHEEL_RUN_REQ: U3.7 (IO3); also elsewhere on the board

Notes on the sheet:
02 / ESP32-S3 module, USB and recovery
DRAFT 0.4 - CIRCUIT DEVELOPMENT ONLY - NOT FOR FABRICATION
GPIO allocation: 38 assigned + GPIO46 boot-low spare. Exact module: ESP32-S3-MINI-1-N8 (no PSRAM). SPI2: ADC1 / optical / IMU / angle / driver config. SPI3: dedicated ADC2. See sheet 09 and gpio-allocation.json. MCPWM0: wheel 3-PWM; MCPWM1: six independent button commands. RMT: one-wire RGB. GPIO3 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
